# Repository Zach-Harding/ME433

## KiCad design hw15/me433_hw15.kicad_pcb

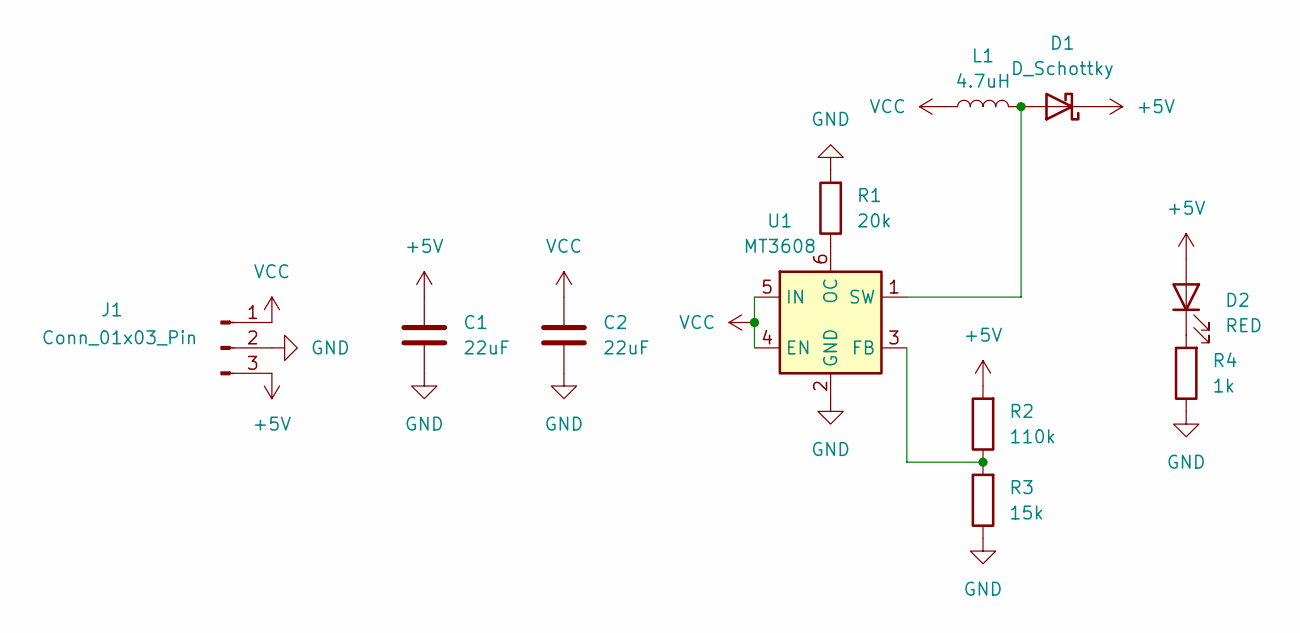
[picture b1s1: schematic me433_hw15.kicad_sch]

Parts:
C1, C2: 22uF; C_0805_2012Metric
D1: D_Schottky; D_SOD-123
D2: RED; LED_0201_0603Metric
J1: Conn_01x03_Pin; PinSocket_1x03_P1.00mm_Vertical
L1: 4.7uH; L_0805_2012Metric
R1: 20k; R_0603_1608Metric
R2: 110k; R_0603_1608Metric
R3: 15k; R_0402_1005Metric
R4: 1k; R_0603_1608Metric
U1: MT3608; SOT-23-6

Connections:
+5V: C1.1, D1.1 (K), D2.2 (A), J1.3, R2.2
GND: C1.2, C2.2, J1.2, R1.2, R3.1, R4.1, U1.2 (GND)
unnamed: D1.2 (A), L1.2, U1.1 (SW)
unnamed: D2.1 (K), R4.2
unnamed: R2.1, R3.2, U1.3 (FB)
unnamed: R1.1, U1.6 (OC)
VCC: C2.1, J1.1, L1.1, U1.4 (EN), U1.5 (IN)

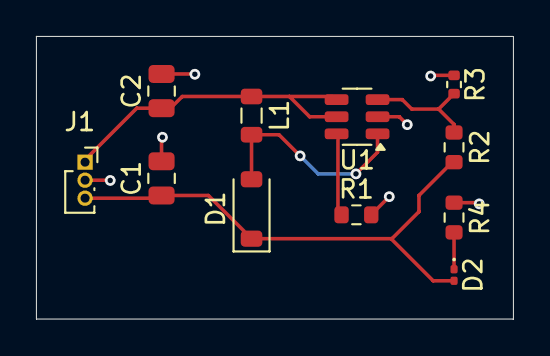
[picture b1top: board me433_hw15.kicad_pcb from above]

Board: 2 copper layers, 26.5 x 15.7 mm, 11 parts (0 on the bottom side), 7 nets.

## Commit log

2025-04-07 hw 2 done
2025-04-08 hw 3 start
2025-04-08 hw 3 outline
2025-04-09 HW3 complete
2025-04-09 hw3 final final
2025-04-11 HW 4 start
2025-04-14 hw4 complete
2025-04-15 hw5 overview
2025-04-16 hw5 (part1 done)
2025-04-16 hw5 done
2025-04-17 hw6 outline
2025-04-17 hw6 start
2025-04-21 hw6 doesn't work and idk why
2025-04-22 hw7 start
2025-04-22 hw6 done
2025-04-28 i hate i2c
2025-04-29 hw 7 done
2025-05-04 hw8 done
2025-05-04 hw9 start
2025-05-04 hw9 done
2025-05-11 hw 10 complete
2025-05-12 hw11 2 buttons work, no circle, no ramping speed
2025-05-20 hw11 complete
2025-05-20 hw11 completed
2025-05-29 hw15 done
2025-05-29 hw14 wheel and screw
2025-06-01 hw13 setup
2025-06-01 hw13 done
2025-06-02 hw12 done
2025-06-02 hw17 offset done (need motor control to implement duty cycles)
2025-06-02 hw16 done
2025-06-02 hw14 finito
2025-06-02 hw14done
2025-06-03 hw16 actually done
2025-06-03 final sorta finished
2025-06-03 final DONE!!!!
2025-06-03 documentation
2025-06-03 pics
